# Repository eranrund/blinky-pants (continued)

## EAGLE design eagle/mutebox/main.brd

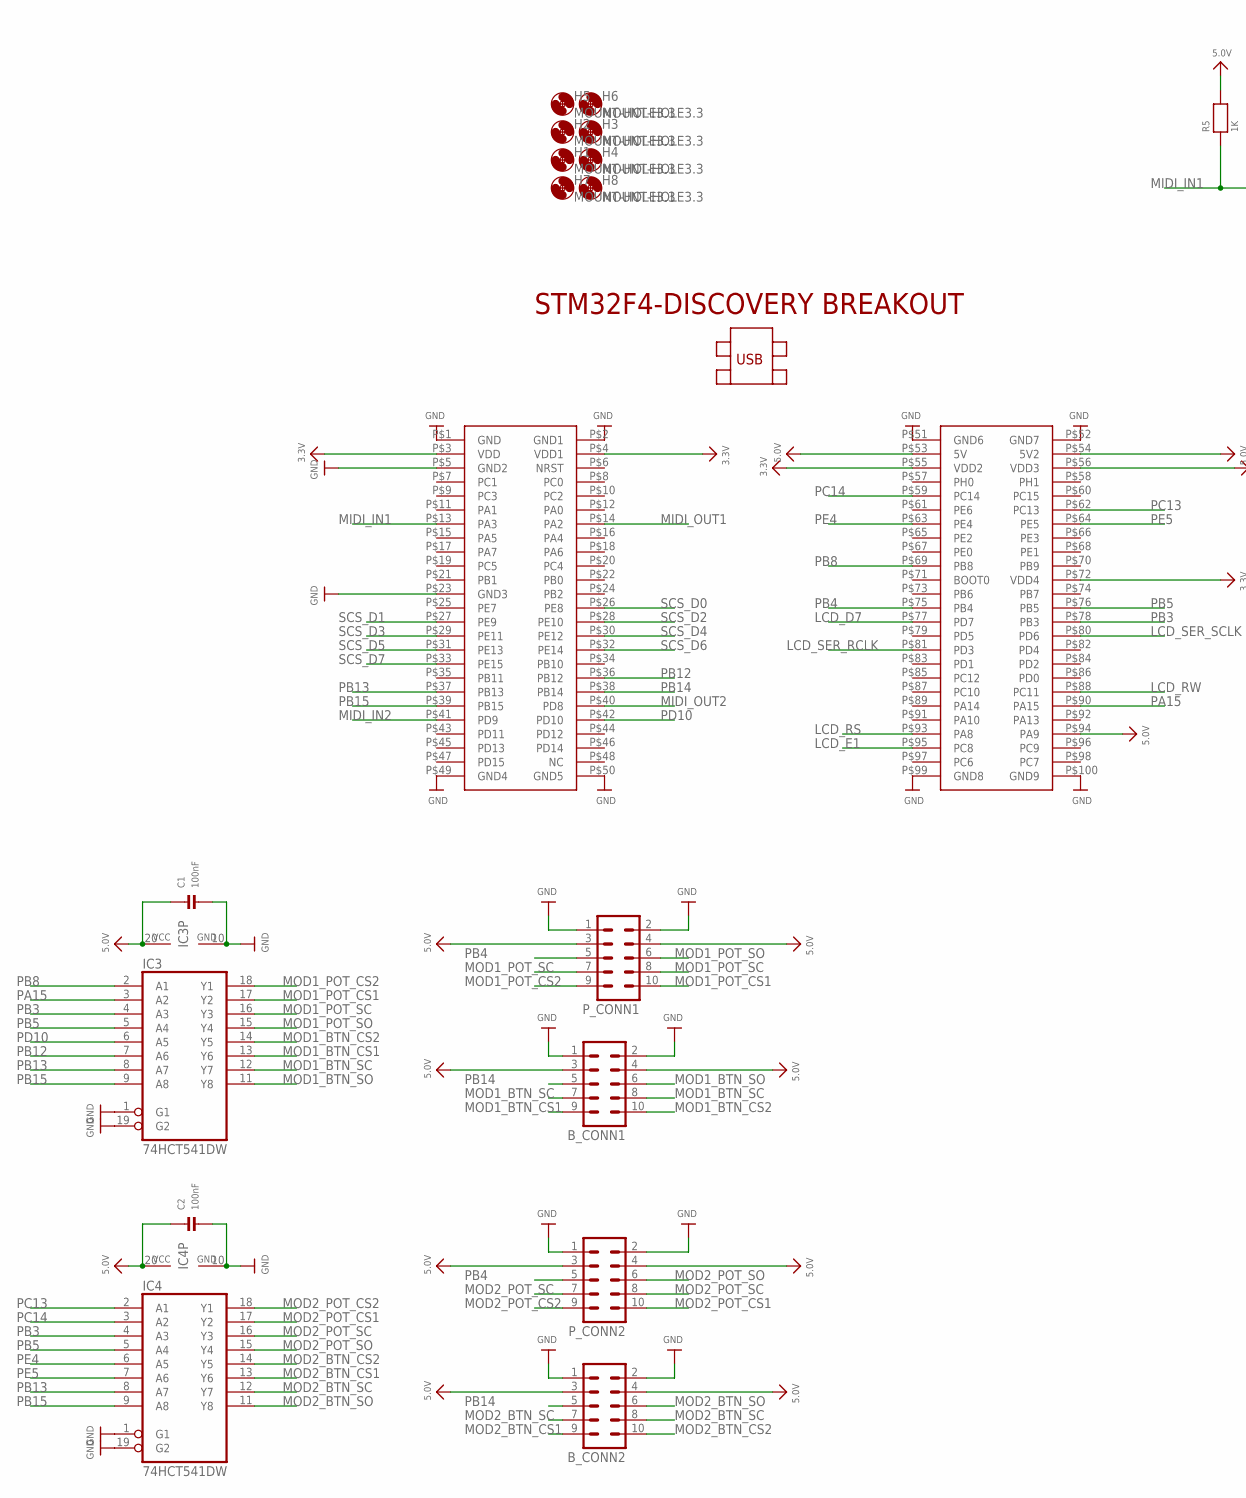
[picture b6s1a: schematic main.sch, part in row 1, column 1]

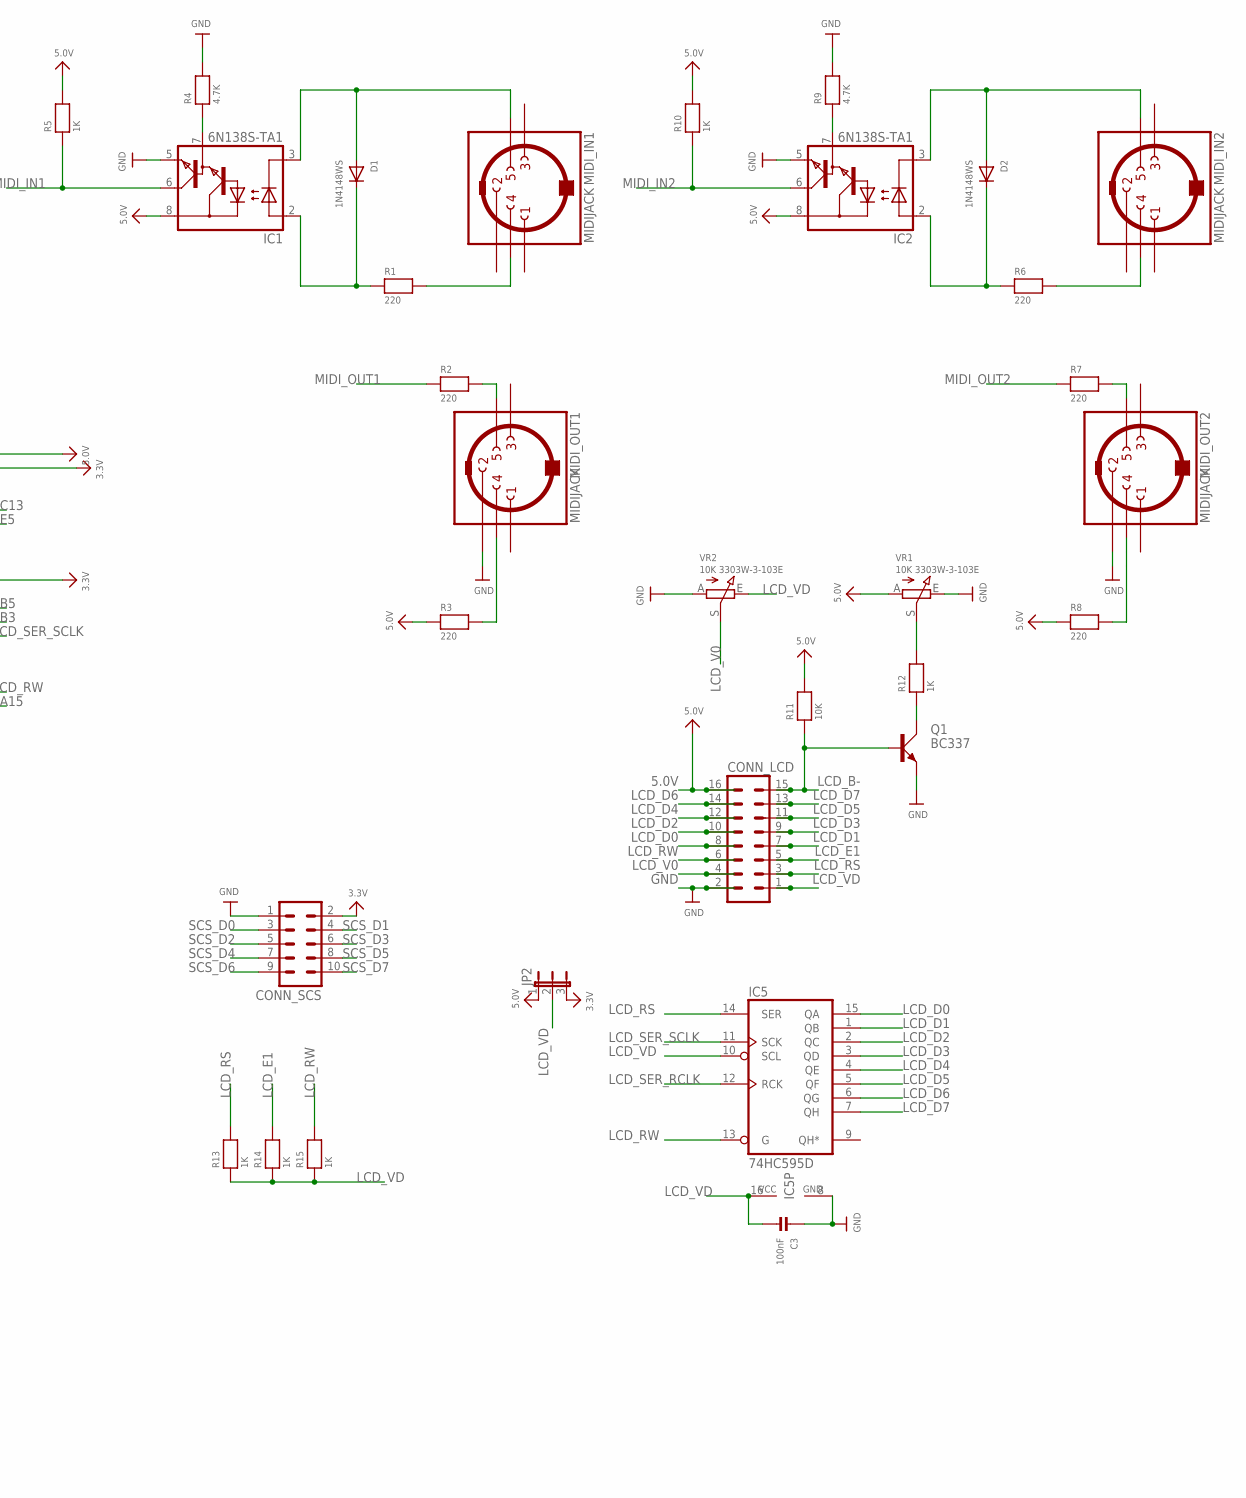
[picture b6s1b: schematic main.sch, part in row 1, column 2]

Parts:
B_CONN1, B_CONN2: ML10
C1, C2, C3: 100nF; 0603
CONN_LCD: ML16
CONN_SCS: ML10
D1, D2: 1N4148WS; SOD-323
H1, H2, H3, H4, H5, H6, H7, H8: MOUNT-HOLE3.3; 3,3
IC1, IC2: 6N138S-TA1; SO8-GW300
IC3, IC4: 74HCT541DW; SO20W
IC5: 74HC595D; SO16
JP2: JUMPER3
MIDI_IN1, MIDI_IN2: MIDIJACK; CP-2350
MIDI_OUT1, MIDI_OUT2: MIDIJACK; CP-2350
P_CONN1, P_CONN2: ML10
Q1: BC337; SOT54A
R1, R2, R3, R6, R7, R8: 220; _0603
R4, R9: 4.7K; _0603
R5, R10, R12, R13, R14, R15: 1K; _0603
R11: 10K; _0603
U$1: STM32F4-DISCOVERY
VR1, VR2: 10K 3303W-3-103E; TRIMPOT_BOURNS3MM

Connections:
3.3V: CONN_SCS.2, JP2.3, U$1.P$3 (VDD), U$1.P$4 (VDD1), U$1.P$55 (VDD2), U$1.P$56 (VDD3), U$1.P$72 (VDD4)
5.0V: B_CONN1.3, B_CONN1.4, B_CONN2.3, B_CONN2.4, C1.1, C2.1, CONN_LCD.16, IC1.8 (VCC), IC2.8 (VCC), IC3.20 (VCC), IC4.20 (VCC), JP2.1, P_CONN1.3, P_CONN1.4, P_CONN2.3, P_CONN2.4, R3.1, R5.2, R8.1, R10.2, R11.2, U$1.P$53 (5V), U$1.P$54 (5V2), U$1.P$94 (PA9), VR1.A
GND: B_CONN1.1, B_CONN1.2, B_CONN2.1, B_CONN2.2, C1.2, C2.2, C3.1, CONN_LCD.2, CONN_SCS.1, IC1.5 (GND), IC2.5 (GND), IC3.1 (G1), IC3.10 (GND), IC3.19 (G2), IC4.1 (G1), IC4.10 (GND), IC4.19 (G2), IC5.8 (GND), MIDI_OUT1.2, MIDI_OUT2.2, P_CONN1.1, P_CONN1.2, P_CONN2.1, P_CONN2.2, Q1.E, R4.2, R9.2, U$1.P$1 (GND), U$1.P$2 (GND1), U$1.P$5 (GND2), U$1.P$23 (GND3), U$1.P$49 (GND4), U$1.P$50 (GND5), U$1.P$51 (GND6), U$1.P$52 (GND7), U$1.P$99 (GND8), U$1.P$100 (GND9), VR1.E, VR2.A
LCD_B-: CONN_LCD.15, Q1.B, R11.1
LCD_D0: CONN_LCD.8, IC5.15 (QA)
LCD_D1: CONN_LCD.7, IC5.1 (QB)
LCD_D2: CONN_LCD.10, IC5.2 (QC)
LCD_D3: CONN_LCD.9, IC5.3 (QD)
LCD_D4: CONN_LCD.12, IC5.4 (QE)
LCD_D5: CONN_LCD.11, IC5.5 (QF)
LCD_D6: CONN_LCD.14, IC5.6 (QG)
LCD_D7: CONN_LCD.13, IC5.7 (QH), U$1.P$77 (PD7)
LCD_E1: CONN_LCD.5, R14.2, U$1.P$95 (PC8)
LCD_RS: CONN_LCD.3, IC5.14 (SER), R13.2, U$1.P$93 (PA8)
LCD_RW: CONN_LCD.6, IC5.13 (G), R15.2, U$1.P$88 (PC11)
LCD_SER_RCLK: IC5.12 (RCK), U$1.P$81 (PD3)
LCD_SER_SCLK: IC5.11 (SCK), U$1.P$80 (PD6)
LCD_V0: CONN_LCD.4, VR2.S
LCD_VD: C3.2, CONN_LCD.1, IC5.10 (SCL), IC5.16 (VCC), JP2.2, R13.1, R14.1, R15.1, VR2.E
MIDI_IN1: IC1.6 (VO), R5.1, U$1.P$13 (PA3)
MIDI_IN2: IC2.6 (VO), R10.1, U$1.P$41 (PD9)
MIDI_OUT1: R2.1, U$1.P$14 (PA2)
MIDI_OUT2: R7.1, U$1.P$40 (PD8)
MOD1_BTN_CS1: B_CONN1.9, IC3.13 (Y6)
MOD1_BTN_CS2: B_CONN1.10, IC3.14 (Y5)
MOD1_BTN_SC: B_CONN1.7, B_CONN1.8, IC3.12 (Y7)
MOD1_BTN_SO: B_CONN1.6, IC3.11 (Y8)
MOD1_POT_CS1: IC3.17 (Y2), P_CONN1.10
MOD1_POT_CS2: IC3.18 (Y1), P_CONN1.9
MOD1_POT_SC: IC3.16 (Y3), P_CONN1.7, P_CONN1.8
MOD1_POT_SO: IC3.15 (Y4), P_CONN1.6
MOD2_BTN_CS1: B_CONN2.9, IC4.13 (Y6)
MOD2_BTN_CS2: B_CONN2.10, IC4.14 (Y5)
MOD2_BTN_SC: B_CONN2.7, B_CONN2.8, IC4.12 (Y7)
MOD2_BTN_SO: B_CONN2.6, IC4.11 (Y8)
MOD2_POT_CS1: IC4.17 (Y2), P_CONN2.10
MOD2_POT_CS2: IC4.18 (Y1), P_CONN2.9
MOD2_POT_SC: IC4.16 (Y3), P_CONN2.7, P_CONN2.8
MOD2_POT_SO: IC4.15 (Y4), P_CONN2.6
unnamed: MIDI_OUT1.5, R2.2
unnamed: MIDI_OUT1.4, R3.2
unnamed: MIDI_IN1.4, R1.2
unnamed: D1.C, IC1.2 (A), R1.1
unnamed: D1.A, IC1.3 (C), MIDI_IN1.5
unnamed: IC1.7 (VB), R4.1
unnamed: Q1.C, R12.1
unnamed: MIDI_OUT2.5, R7.2
unnamed: MIDI_OUT2.4, R8.2
unnamed: MIDI_IN2.4, R6.2
unnamed: D2.C, IC2.2 (A), R6.1
unnamed: D2.A, IC2.3 (C), MIDI_IN2.5
unnamed: IC2.7 (VB), R9.1
unnamed: R12.2, VR1.S
PA15: IC3.3 (A2), U$1.P$90 (PA15)
PB3: IC3.4 (A3), IC4.4 (A3), U$1.P$78 (PB3)
PB4: P_CONN1.5, P_CONN2.5, U$1.P$75 (PB4)
PB5: IC3.5 (A4), IC4.5 (A4), U$1.P$76 (PB5)
PB8: IC3.2 (A1), U$1.P$69 (PB8)
PB12: IC3.7 (A6), U$1.P$36 (PB12)
PB13: IC3.8 (A7), IC4.8 (A7), U$1.P$37 (PB13)
PB14: B_CONN1.5, B_CONN2.5, U$1.P$38 (PB14)
PB15: IC3.9 (A8), IC4.9 (A8), U$1.P$39 (PB15)
PC13: IC4.2 (A1), U$1.P$62 (PC13)
PC14: IC4.3 (A2), U$1.P$59 (PC14)
PD10: IC3.6 (A5), U$1.P$42 (PD10)
PE4: IC4.6 (A5), U$1.P$63 (PE4)
PE5: IC4.7 (A6), U$1.P$64 (PE5)
SCS_D0: CONN_SCS.3, U$1.P$26 (PE8)
SCS_D1: CONN_SCS.4, U$1.P$27 (PE9)
SCS_D2: CONN_SCS.5, U$1.P$28 (PE10)
SCS_D3: CONN_SCS.6, U$1.P$29 (PE11)
SCS_D4: CONN_SCS.7, U$1.P$30 (PE12)
SCS_D5: CONN_SCS.8, U$1.P$31 (PE13)
SCS_D6: CONN_SCS.9, U$1.P$32 (PE14)
SCS_D7: CONN_SCS.10, U$1.P$33 (PE15)

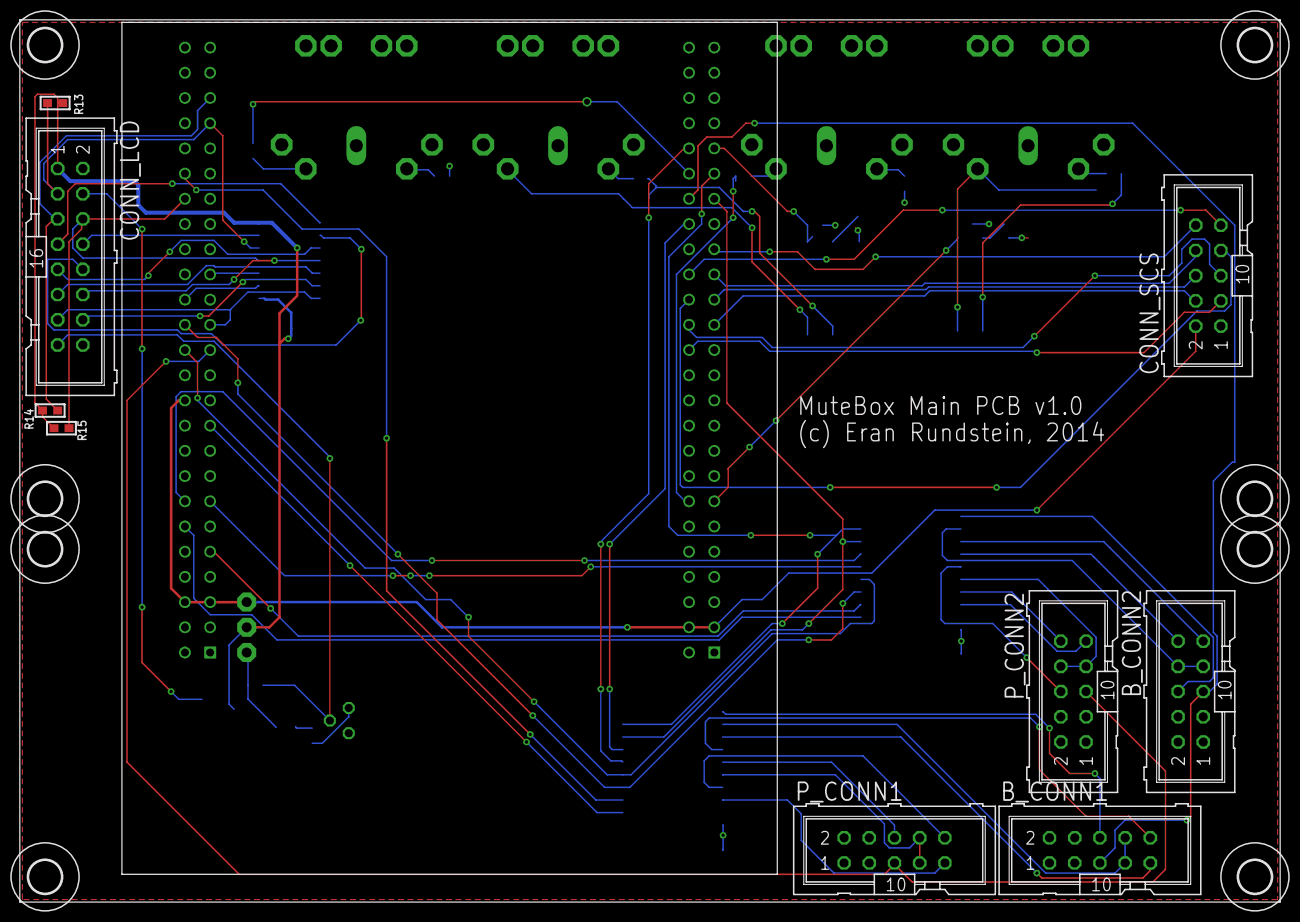
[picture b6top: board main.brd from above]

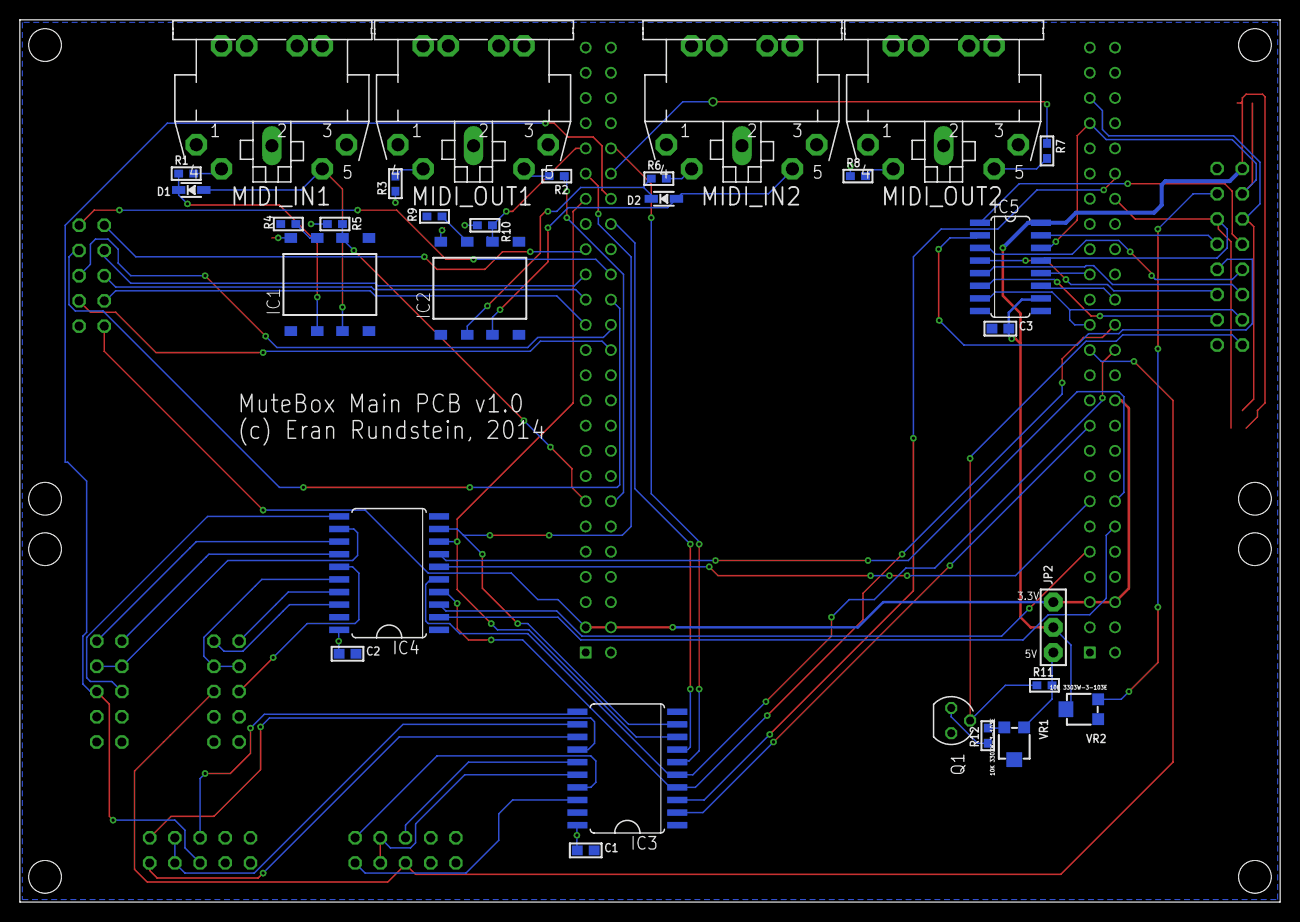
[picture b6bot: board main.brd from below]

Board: 2 copper layers, 127.0 x 88.9 mm, 48 parts (30 on the bottom side), 75 nets.

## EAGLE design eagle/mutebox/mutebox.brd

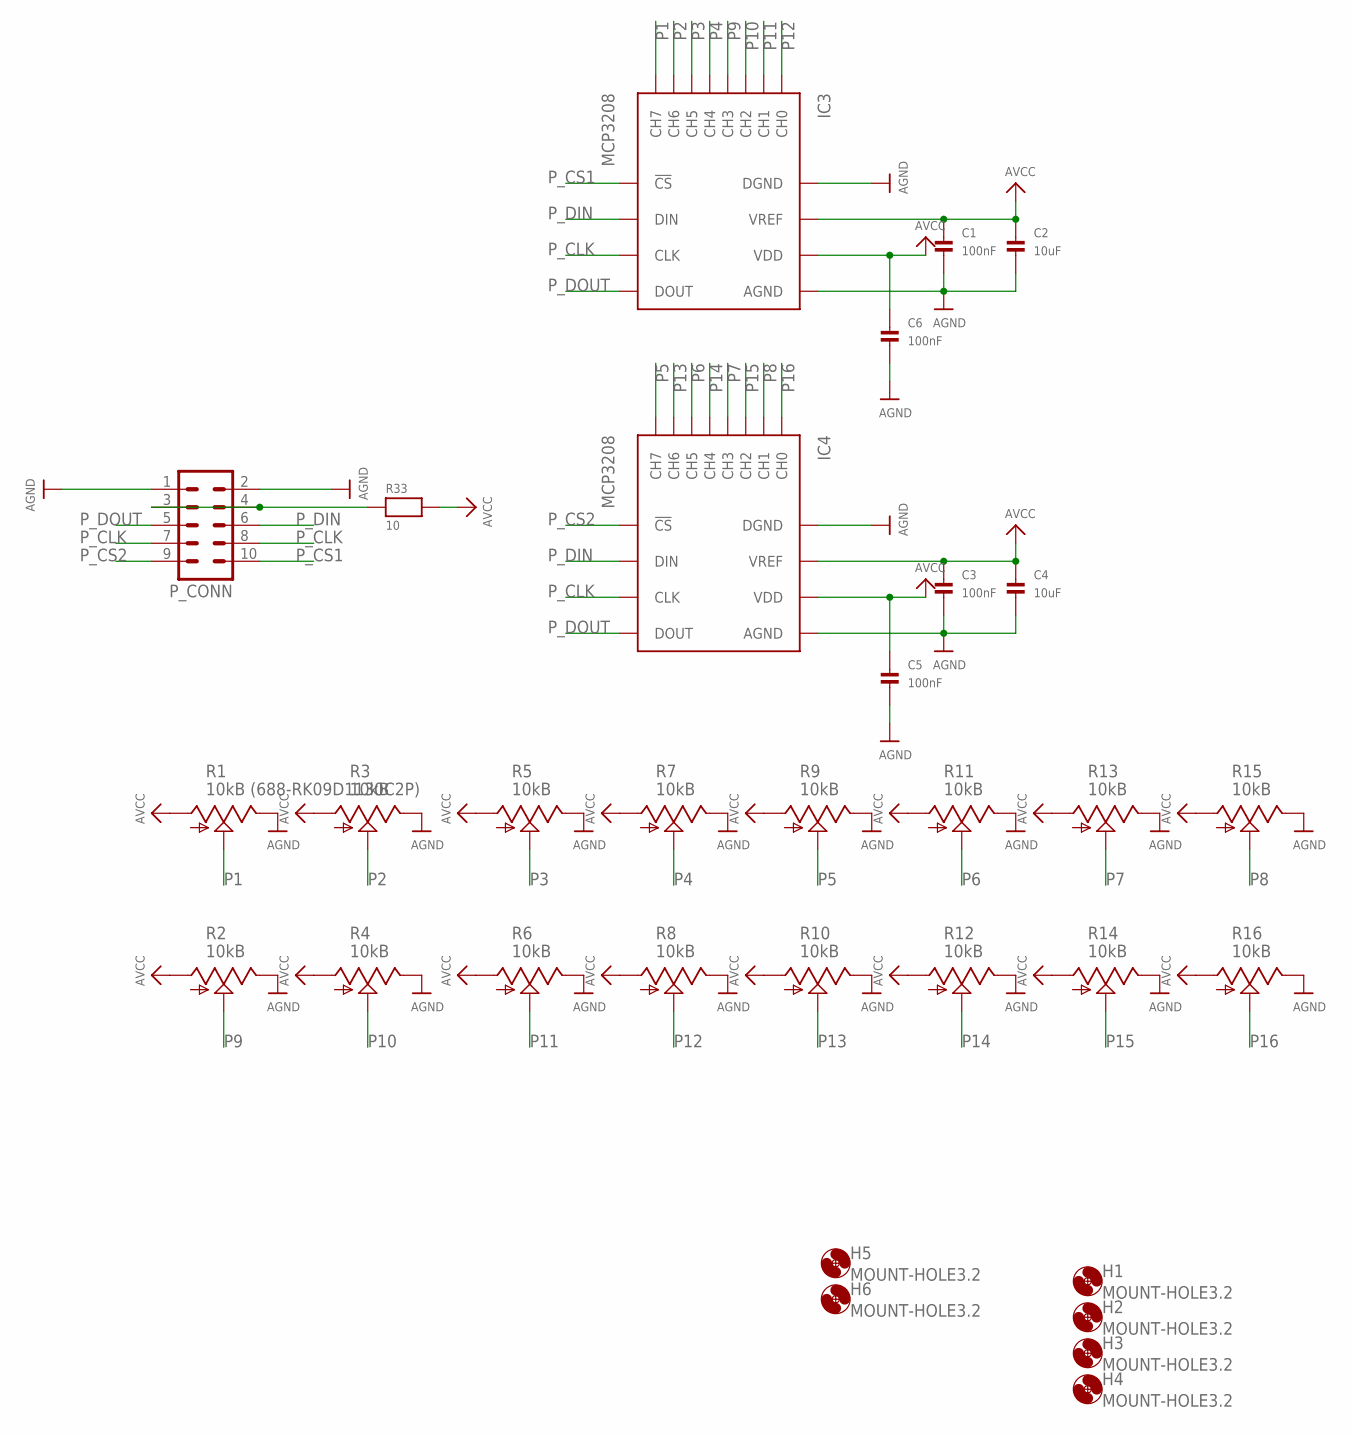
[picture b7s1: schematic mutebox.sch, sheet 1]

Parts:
C1, C3, C5, C6: 100nF; 0603
C2, C4: 10uF; _0805
H1, H2, H3, H4, H5, H6: MOUNT-HOLE3.2; 3,2
IC3, IC4: MCP3208; PDIP16
P_CONN: ML10
R1: 10kB (688-RK09D1130C2P); ALPS_POT_VERTICAL_PS
R2, R3, R4, R5, R6, R7, R8, R9, R10, R11, R12, R13, R14, R15, R16: 10kB; ALPS_POT_VERTICAL_PS
R33: 10; _0805

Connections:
AGND: C1.2, C2.2, C3.2, C4.2, C5.2, C6.2, IC3.P$9 (DGND), IC3.P$14 (AGND), IC4.P$9 (DGND), IC4.P$14 (AGND), P_CONN.1, P_CONN.2, R1.P$1 (E), R2.P$1 (E), R3.P$1 (E), R4.P$1 (E), R5.P$1 (E), R6.P$1 (E), R7.P$1 (E), R8.P$1 (E), R9.P$1 (E), R10.P$1 (E), R11.P$1 (E), R12.P$1 (E), R13.P$1 (E), R14.P$1 (E), R15.P$1 (E), R16.P$1 (E)
AVCC: C1.1, C2.1, C3.1, C4.1, C5.1, C6.1, IC3.P$15 (VREF), IC3.P$16 (VDD), IC4.P$15 (VREF), IC4.P$16 (VDD), R1.P$3 (A), R2.P$3 (A), R3.P$3 (A), R4.P$3 (A), R5.P$3 (A), R6.P$3 (A), R7.P$3 (A), R8.P$3 (A), R9.P$3 (A), R10.P$3 (A), R11.P$3 (A), R12.P$3 (A), R13.P$3 (A), R14.P$3 (A), R15.P$3 (A), R16.P$3 (A), R33.2
unnamed: P_CONN.3, P_CONN.4, R33.1
P1: IC3.P$8 (CH7), R1.P$2 (S)
P2: IC3.P$7 (CH6), R3.P$2 (S)
P3: IC3.P$6 (CH5), R5.P$2 (S)
P4: IC3.P$5 (CH4), R7.P$2 (S)
P5: IC4.P$8 (CH7), R9.P$2 (S)
P6: IC4.P$6 (CH5), R11.P$2 (S)
P7: IC4.P$4 (CH3), R13.P$2 (S)
P8: IC4.P$2 (CH1), R15.P$2 (S)
P9: IC3.P$4 (CH3), R2.P$2 (S)
P10: IC3.P$3 (CH2), R4.P$2 (S)
P11: IC3.P$2 (CH1), R6.P$2 (S)
P12: IC3.P$1 (CH0), R8.P$2 (S)
P13: IC4.P$7 (CH6), R10.P$2 (S)
P14: IC4.P$5 (CH4), R12.P$2 (S)
P15: IC4.P$3 (CH2), R14.P$2 (S)
P16: IC4.P$1 (CH0), R16.P$2 (S)
P_CLK: IC3.P$13 (CLK), IC4.P$13 (CLK), P_CONN.7, P_CONN.8
P_CS1: IC3.P$10 (!CS), P_CONN.10
P_CS2: IC4.P$10 (!CS), P_CONN.9
P_DIN: IC3.P$11 (DIN), IC4.P$11 (DIN), P_CONN.6
P_DOUT: IC3.P$12 (DOUT), IC4.P$12 (DOUT), P_CONN.5

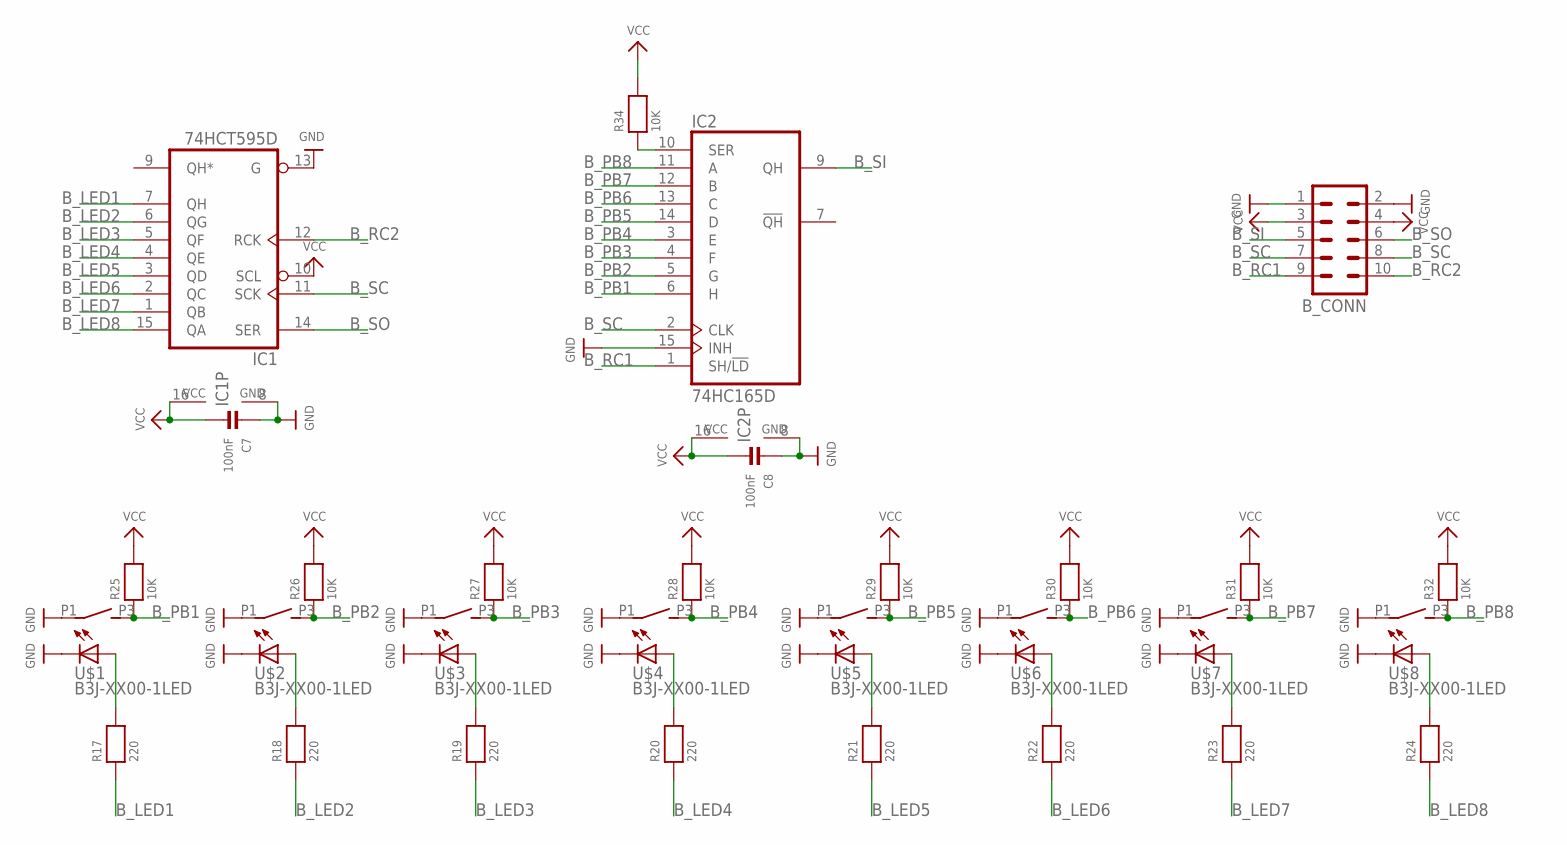
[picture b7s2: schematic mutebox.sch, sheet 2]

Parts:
B_CONN: ML10
C7, C8: 100nF; 0603
IC1: 74HCT595D; SO16
IC2: 74HC165D; SO16
R17, R18, R19, R20, R21, R22, R23, R24: 220; _0603
R25, R26, R27, R28, R29, R30, R31, R32, R34: 10K; _0603
U$1, U$2, U$3, U$4, U$5, U$6, U$7, U$8: B3J-XX00-1LED

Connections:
B_LED1: IC1.7 (QH), R17.1
B_LED2: IC1.6 (QG), R18.1
B_LED3: IC1.5 (QF), R19.1
B_LED4: IC1.4 (QE), R20.1
B_LED5: IC1.3 (QD), R21.1
B_LED6: IC1.2 (QC), R22.1
B_LED7: IC1.1 (QB), R23.1
B_LED8: IC1.15 (QA), R24.1
B_PB1: IC2.6 (H), R25.1, U$1.P3 (SW2)
B_PB2: IC2.5 (G), R26.1, U$2.P3 (SW2)
B_PB3: IC2.4 (F), R27.1, U$3.P3 (SW2)
B_PB4: IC2.3 (E), R28.1, U$4.P3 (SW2)
B_PB5: IC2.14 (D), R29.1, U$5.P3 (SW2)
B_PB6: IC2.13 (C), R30.1, U$6.P3 (SW2)
B_PB7: IC2.12 (B), R31.1, U$7.P3 (SW2)
B_PB8: IC2.11 (A), R32.1, U$8.P3 (SW2)
B_RC1: B_CONN.9, IC2.1 (SH/!LD)
B_RC2: B_CONN.10, IC1.12 (RCK)
B_SC: B_CONN.7, B_CONN.8, IC1.11 (SCK), IC2.2 (CLK)
B_SI: B_CONN.5, IC2.9 (QH)
B_SO: B_CONN.6, IC1.14 (SER)
GND: B_CONN.1, B_CONN.2, C7.1, C8.1, IC1.8 (GND), IC1.13 (G), IC2.8 (GND), IC2.15 (INH), U$1.LED-, U$1.P1 (SW1), U$2.LED-, U$2.P1 (SW1), U$3.LED-, U$3.P1 (SW1), U$4.LED-, U$4.P1 (SW1), U$5.LED-, U$5.P1 (SW1), U$6.LED-, U$6.P1 (SW1), U$7.LED-, U$7.P1 (SW1), U$8.LED-, U$8.P1 (SW1)
unnamed: R17.2, U$1.LED+
unnamed: R18.2, U$2.LED+
unnamed: R19.2, U$3.LED+
unnamed: R20.2, U$4.LED+
unnamed: R21.2, U$5.LED+
unnamed: R22.2, U$6.LED+
unnamed: R23.2, U$7.LED+
unnamed: R24.2, U$8.LED+
unnamed: IC2.10 (SER), R34.1
VCC: B_CONN.3, B_CONN.4, C7.2, C8.2, IC1.10 (SCL), IC1.16 (VCC), IC2.16 (VCC), R25.2, R26.2, R27.2, R28.2, R29.2, R30.2, R31.2, R32.2, R34.2

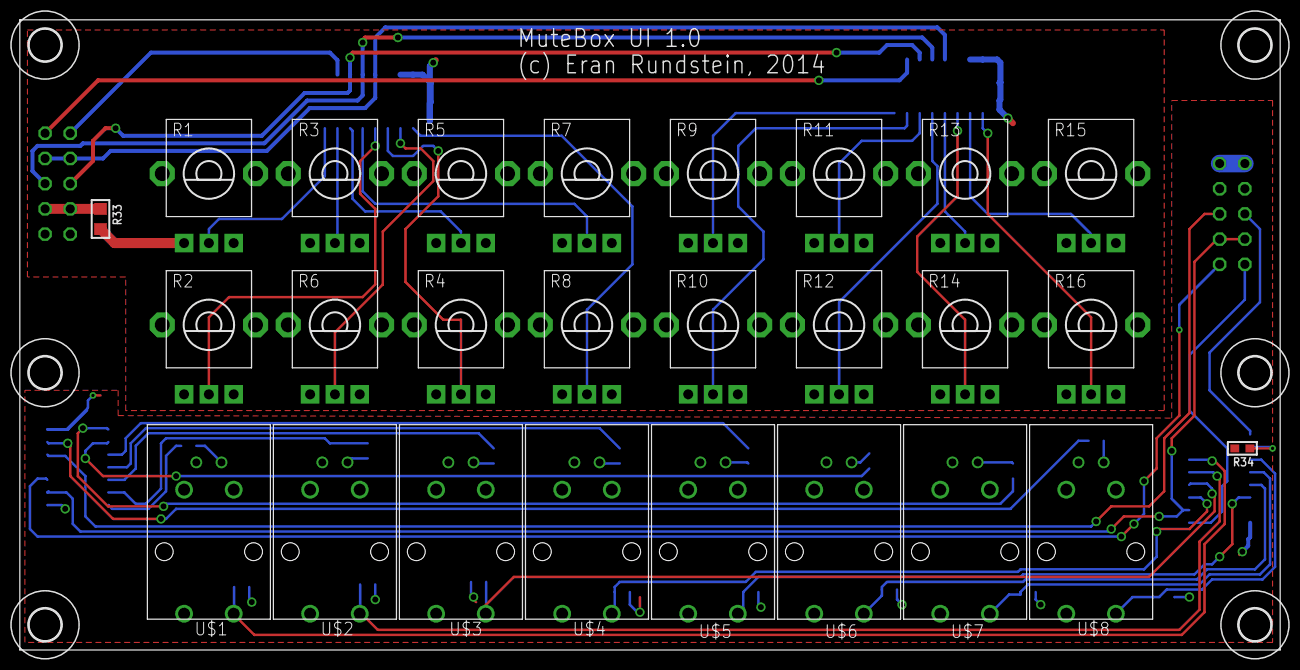
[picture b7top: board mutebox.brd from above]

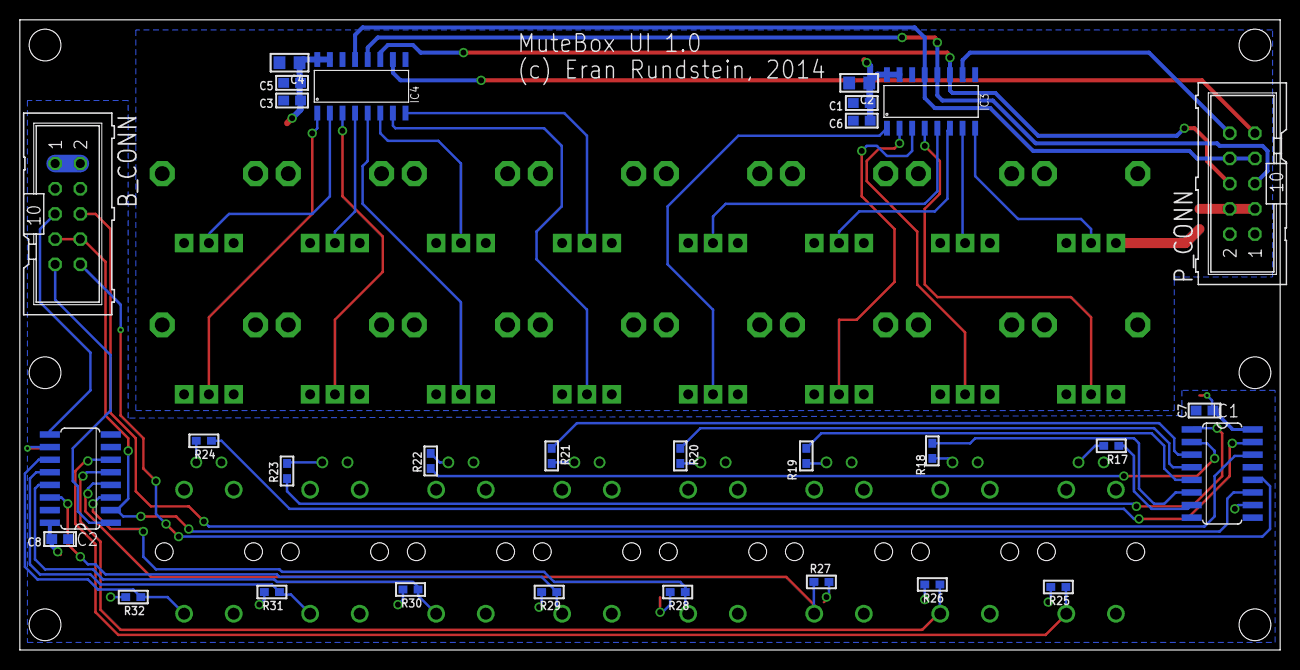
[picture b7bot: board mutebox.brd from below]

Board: 2 copper layers, 127.0 x 63.5 mm, 62 parts (30 on the bottom side), 56 nets.

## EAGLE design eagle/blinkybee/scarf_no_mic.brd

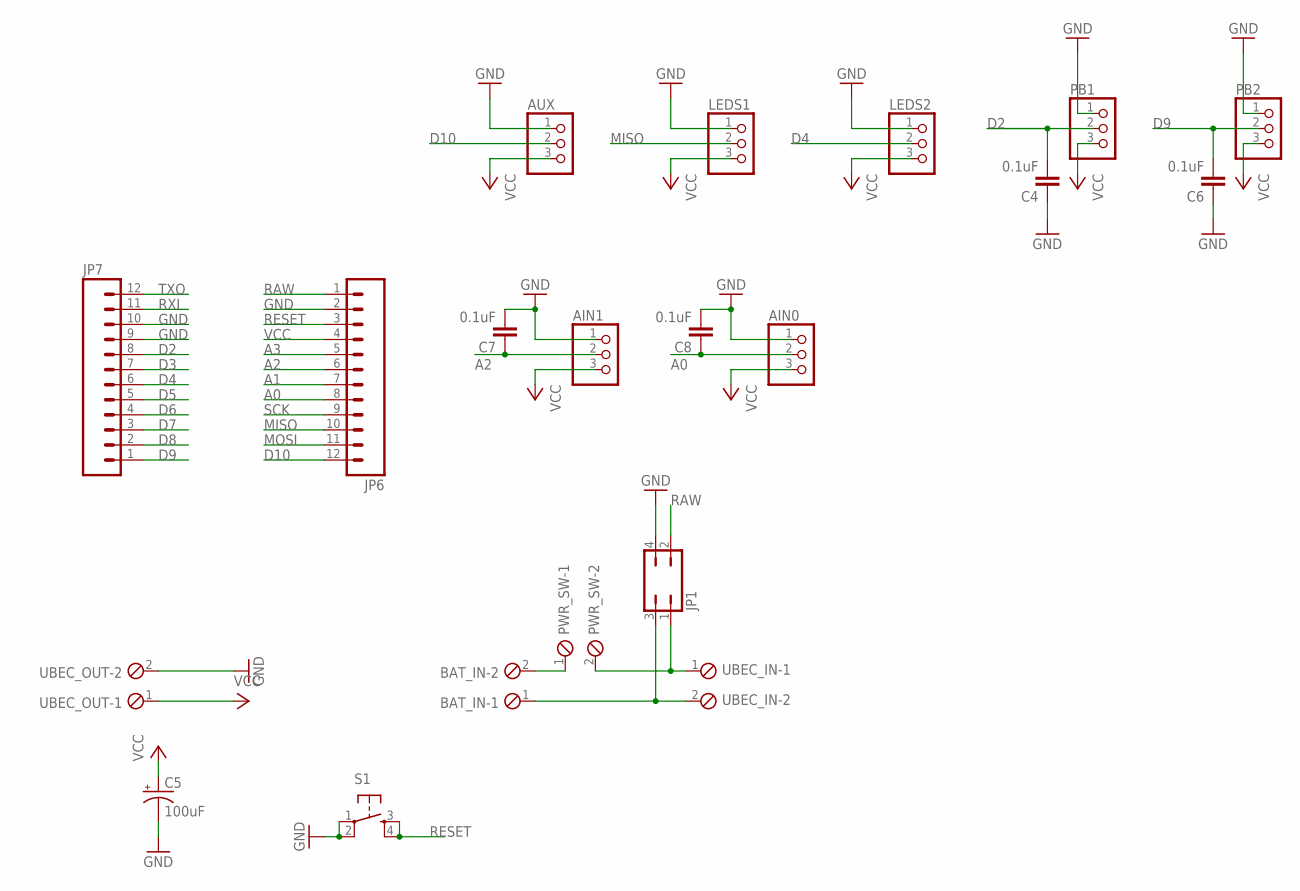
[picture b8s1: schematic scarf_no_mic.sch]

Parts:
AIN0, AIN1: HEADER-1X3ROUND; 1X03_ROUND
AUX: HEADER-1X3ROUND; 1X03_ROUND
BAT_IN: MPT2; 2POL254
C4, C6, C7, C8: 0.1uF; C025-025X050
C5: 100uF; E3,5-8
JP1: JP2Q
JP6, JP7: M12PTH; 1X12
LEDS1, LEDS2: PINHD-1X3; 1X03
PB1, PB2: HEADER-1X3ROUND; 1X03_ROUND
PWR_SW: MPT2; 2POL254
S1: TAC_SWITCHPTH; TACTILE-PTH
UBEC_IN: MPT2; 2POL254
UBEC_OUT: MPT2; 2POL254

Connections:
A0: AIN0.2, C8.1, JP6.8
A1: JP6.7
A2: AIN1.2, C7.1, JP6.6
A3: JP6.5
D2: C4.2, JP7.8, PB1.2
D3: JP7.7
D4: JP7.6, LEDS2.2
D5: JP7.5
D6: JP7.4
D7: JP7.3
D8: JP7.2
D9: C6.2, JP7.1, PB2.2
D10: AUX.2, JP6.12
GND: AIN0.1, AIN1.1, AUX.1, C4.1, C5.-, C6.1, C7.2, C8.2, JP1.4, JP6.2, JP7.9, JP7.10, LEDS1.1, LEDS2.1, PB1.1, PB2.1, S1.1, S1.2, UBEC_OUT.2
MISO: JP6.10, LEDS1.2
MOSI: JP6.11
unnamed: BAT_IN.2, PWR_SW.1
unnamed: JP1.1, PWR_SW.2, UBEC_IN.1
unnamed: BAT_IN.1, JP1.3, UBEC_IN.2
RAW: JP1.2, JP6.1
RESET: JP6.3, S1.3, S1.4
RXI: JP7.11
SCK: JP6.9
TXO: JP7.12
VCC: AIN0.3, AIN1.3, AUX.3, C5.+, JP6.4, LEDS1.3, LEDS2.3, PB1.3, PB2.3, UBEC_OUT.1

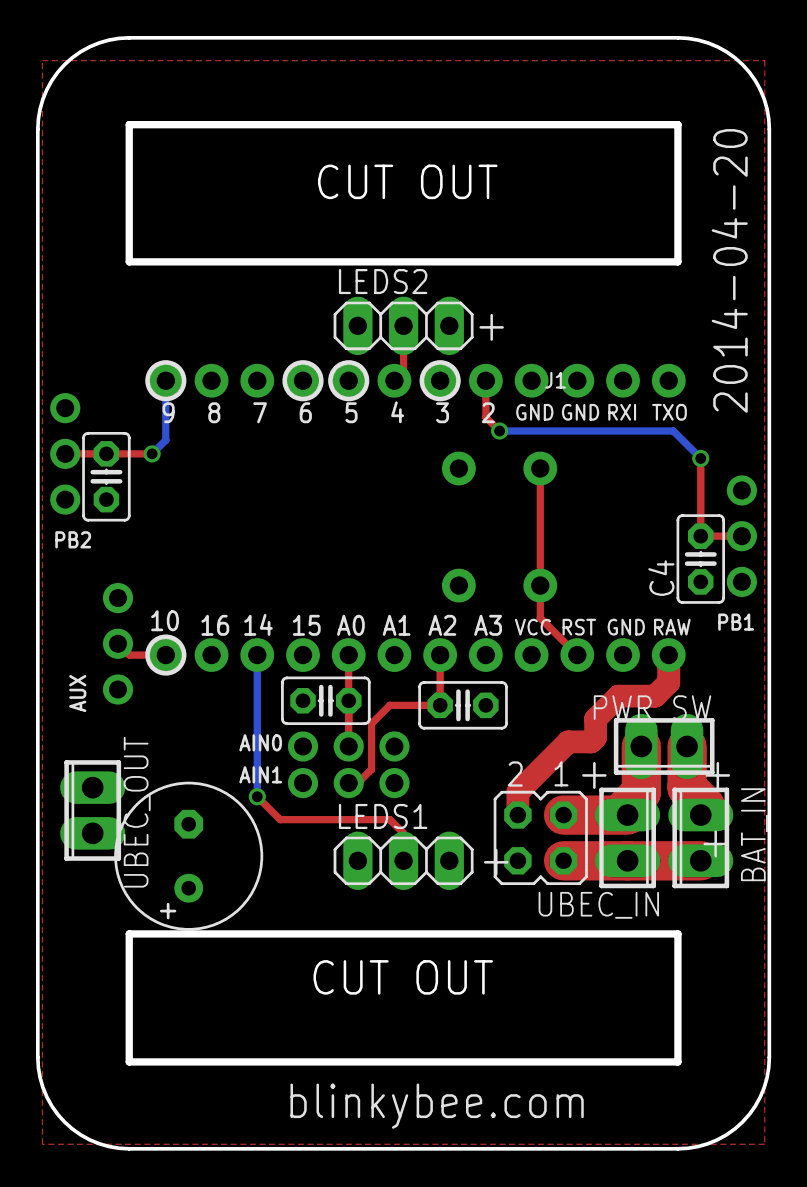
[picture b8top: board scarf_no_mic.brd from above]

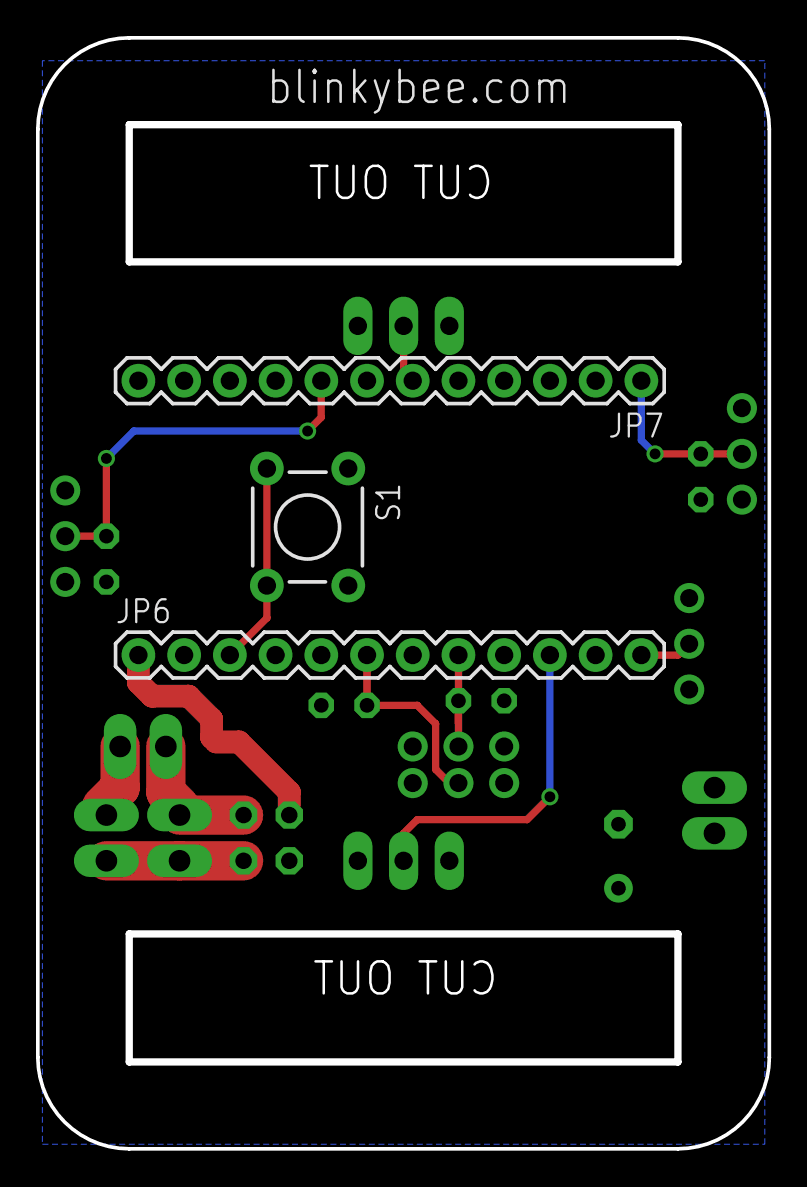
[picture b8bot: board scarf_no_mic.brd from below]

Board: 2 copper layers, 40.6 x 61.7 mm, 20 parts (3 on the bottom side), 14 nets.

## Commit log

2013-12-05 skeleton
2013-12-21 christmas stuff
2013-12-21 + my hsv patterns
2013-12-21 more efx
2013-12-21 first working version
2013-12-24 lpd-raspberry
2013-12-26 VERY GOOD VERSION :D
2013-12-26 minor improvement
2014-01-02 blinky pants rotary encoder poc
2014-01-02 nicer pants code with brightness pot + pattern rotenc
2014-01-02 before speed mess
2014-01-02 support for speed pot
2014-01-23 before autorouter
2014-01-23 first ver routing
2014-01-31 pcb simplification - remove dual rot/pot
2014-01-31 board stuff
2014-02-24 organize
2014-02-24 arduino pro micro template
2014-02-24 zxsound
2014-02-24 mic layout take 2
2014-03-02 serial-mapper
2014-03-04 pants v2 before custom patterns for pants
2014-03-04 pattern 1
2014-03-04 shootrings, ringshsv
2014-03-04 spinning rings
2014-03-07 scarf cap wip
2014-03-08 pants v2 speed tuning so that speed knob can be at the middle
2014-03-15 make pants version selection in runtime
2014-03-20 scarf pcb
2014-03-22 scarf v2014-03-22 sent to oshpark
2014-03-23 add mic mode
2014-03-23 speedup @ ring pattern
2014-03-29 camelbak
2014-04-02 add stuff
2014-04-02 BIG REWORK
2014-04-04 cleanups
2014-04-04 maybe breaking
2014-04-09 teensy
2014-04-18 hat + mpu
2014-04-18 hat + gyro
2014-04-19 pants fixups
2014-04-19 camelbak fixes
2014-04-19 merge:
2014-04-19 scarf without mic pcb
2014-04-19 small fix
2014-04-23 vest before autorouter
2014-04-23 vest pcb v1
2014-04-23 vest+ctrl board
2014-04-23 jacket teensy code 'ported' from pants - works but timing sux
2014-04-23 attempted to upgrade to fastled2.1, seems flickering
2014-04-25 scarf without mic pcb v1
2014-04-30 vest
2014-04-30 vest map
2014-05-08 Added FAstLED lib (????? wtf), rvtow, nightlight
2014-05-09 vest pcb is working
2014-05-10 vest wip
2014-05-12 nightlight: increase timer
2014-05-12 vest wip in good state
2014-05-12 bleh
2014-05-16 en/dis jumper for vest control board
2014-05-19 update vest led count
2014-05-19 vest audio failed fft
2014-06-16 furcoat
2014-06-16 matrix_furcoat
2014-06-24 fix rvrow
2014-06-25 bicycle v1
2014-06-25 bicycle + fastled with color palette
2014-06-25 vest: fastled with color palette demo added
2014-07-09 wipwip
2014-11-01 mutebox
2014-11-06 mutebox: connectors now match midibox
2014-11-06 mutebox: rearranged leds
2014-11-12 muteboxwip
2014-11-25 mutebox main: shrouded connectors
2014-11-27 mutebox rearrange buttons
2015-01-07 models
2015-01-07 WTF CHANGES IN BOARD???
2015-01-21 case
2015-01-23 more case work
2015-01-24 swbox_midi
2015-02-06 route mutebox scs
2015-03-13 bom-ex_wip
2015-03-15 partsdb
2015-12-30 staff wip
